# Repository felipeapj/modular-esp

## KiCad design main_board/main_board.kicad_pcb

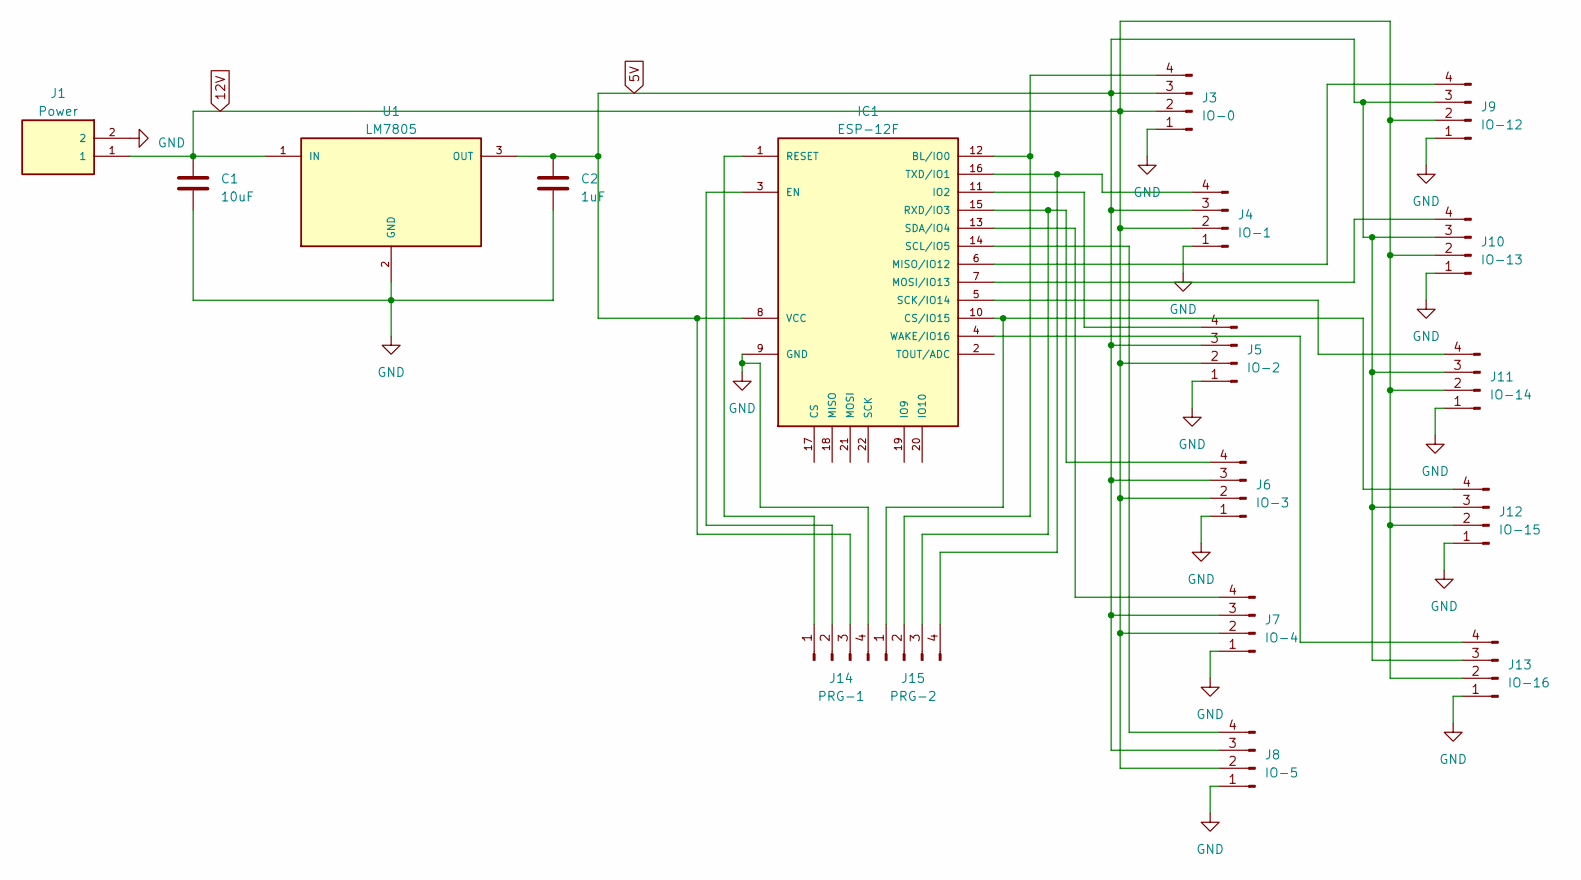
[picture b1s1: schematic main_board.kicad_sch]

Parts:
C1: 10uF; CP_Radial_D5.0mm_P2.50mm
C2: 1uF; CP_Radial_D5.0mm_P2.50mm
IC1: ESP-12F
J1: Power; CUI_TB008A-508-02GR
J3: IO-0; JST_EH_B4B-EH-A_1x04_P2.50mm_Vertical
J4: IO-1; JST_EH_B4B-EH-A_1x04_P2.50mm_Vertical
J5: IO-2; JST_EH_B4B-EH-A_1x04_P2.50mm_Vertical
J6: IO-3; JST_EH_B4B-EH-A_1x04_P2.50mm_Vertical
J7: IO-4; JST_EH_B4B-EH-A_1x04_P2.50mm_Vertical
J8: IO-5; JST_EH_B4B-EH-A_1x04_P2.50mm_Vertical
J9: IO-12; JST_EH_B4B-EH-A_1x04_P2.50mm_Vertical
J10: IO-13; JST_EH_B4B-EH-A_1x04_P2.50mm_Vertical
J11: IO-14; JST_EH_B4B-EH-A_1x04_P2.50mm_Vertical
J12: IO-15; JST_EH_B4B-EH-A_1x04_P2.50mm_Vertical
J13: IO-16; JST_EH_B4B-EH-A_1x04_P2.50mm_Vertical
J14: PRG-1; JST_EH_B4B-EH-A_1x04_P2.50mm_Vertical
J15: PRG-2; JST_EH_B4B-EH-A_1x04_P2.50mm_Vertical
U1: LM7805; TO254P1054X470X1955-3

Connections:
5V: C2.1, IC1.8 (VCC), J3.3, J4.3, J5.3, J6.3, J7.3, J8.3, J9.3, J10.3, J11.3, J12.3, J13.3, J14.3, U1.3 (OUT)
12V: C1.1, J1.1, J3.2, J4.2, J5.2, J6.2, J7.2, J8.2, J9.2, J10.2, J11.2, J12.2, J13.2, U1.1 (IN)
GND: C1.2, C2.2, IC1.9 (GND), J1.2, J3.1, J4.1, J5.1, J6.1, J7.1, J8.1, J9.1, J10.1, J11.1, J12.1, J13.1, J14.4, U1.2 (GND)
unnamed: IC1.12 (BL/IO0), J3.4, J15.2
unnamed: IC1.10 (CS/IO15), J12.4, J15.1
unnamed: IC1.3 (EN), J14.2
unnamed: IC1.11 (IO2), J5.4
unnamed: IC1.6 (MISO/IO12), J9.4
unnamed: IC1.7 (MOSI/IO13), J10.4
unnamed: IC1.1 (RESET), J14.1
unnamed: IC1.15 (RXD/IO3), J6.4, J15.3
unnamed: IC1.5 (SCK/IO14), J11.4
unnamed: IC1.14 (SCL/IO5), J8.4
unnamed: IC1.13 (SDA/IO4), J7.4
unnamed: IC1.16 (TXD/IO1), J4.4, J15.4
unnamed: IC1.4 (WAKE/IO16), J13.4

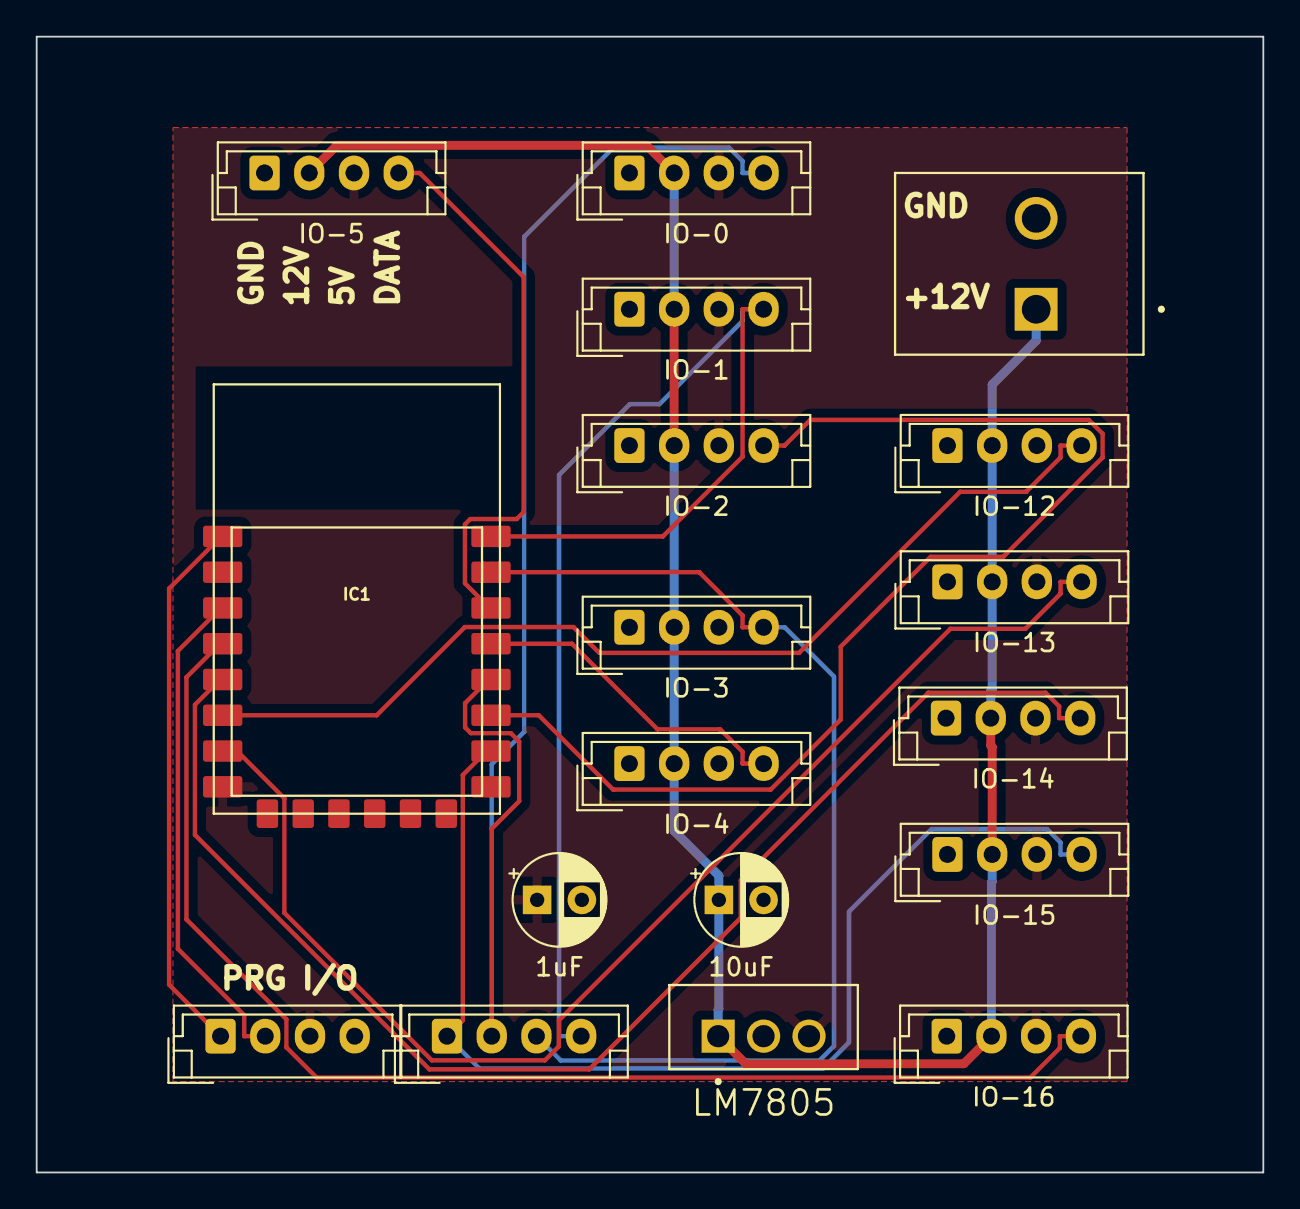
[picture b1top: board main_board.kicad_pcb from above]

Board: 2 copper layers, 68.6 x 63.5 mm, 18 parts (0 on the bottom side), 16 nets.
